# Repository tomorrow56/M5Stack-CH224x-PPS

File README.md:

# M5Stack-CH224x-PPS

An Arduino library and sample sketch collection for controlling CH224A/CH224Q USB PD controllers via I2C on M5Stack (M5Unified compatible), with USB PD PPS/AVS mode voltage adjustment.

## Features

- **Fixed Voltage Mode**: Select from 5V/9V/12V/15V/20V/28V fixed voltages
- **PPS Mode**: Adjust voltage in 0.1V steps within 5.0V～21.0V range
- **AVS Mode**: Variable voltage setting (16-bit precision)
- **Source Capabilities Analysis**: Detailed display of SRCCAP/EPR_SRCCAP messages
- **PDO Type Identification**: Automatic detection of Fixed/Battery/Variable/PPS Supply
- **CH224A Library**: Reusable library class (`src/CH224A.h`)

## Project Structure

```text
M5Stack-CH224x-PPS/
├── src/
│   ├── CH224A.h          # CH224A library header
│   └── CH224A.cpp        # CH224A library implementation
├── examples/
│   ├── M5Stack_PDtrigger_PPS/             # PD Analyzer with PDO decode
│   └── test/                              # Test and debug sketches
│       ├── M5Stack_CH224A_PPS/            # PPS voltage control (with GUI)
│       ├── CH224A_PDO_Test/               # PDO decode test (serial output)
│       ├── I2C_Scanner/                   # I2C device scanner
│       ├── PPS_Test/                      # PPS voltage sweep test
│       └── Simple_Test/                   # Fixed voltage auto-switch test
├── kicad/                                 # KiCad design files
│   └── M5_PDtrigger_PPS_v2/               # Hardware design v2
├── case/                                  # 3D printable case files
│   └── M5Stack_PDtrigger/                 # M5Stack PD Trigger case
├── README_JP.md           # Japanese documentation
├── README.md             # This file
├── WIRING.md             # Detailed wiring information
└── LICENSE               # MIT license
```

## Hardware Requirements

### Required Components

- **M5Stack** (M5Unified compatible device: Core Basic, Core2, CoreS3, etc.)
- **CH224A/CH224Q** USB PD controller (ESSOP10/DFN10 package)
- **USB Type-C connector**
- **1μF ceramic capacitor** (between VHV-GND)

### Pin Connections

| M5Stack       | CH224A          | Description               |
|---------------|-----------------|---------------------------|
| GPIO21        | Pin 3 (CFG3/SDA)| I2C data line            |
| GPIO22        | Pin 2 (CFG2/SCL)| I2C clock line           |
| GND           | Pin 0 (GND)     | Ground                   |
| GPIO2 (※)    | VBUSEN          | Output enable            |
| GPIO12 (※)   | Pin 10 (PG)     | Power Good input         |

※ Used in sample sketches. Can be changed according to your purpose.

**Important**: When using CFG2/CFG3 pins as I2C, do not connect resistors to these pins (leave them floating).

For detailed wiring information, see [WIRING.md](WIRING.md).

## 3D Printable Case

A custom 3D printable case is available for the M5Stack PD Trigger:

### Files Available

- **`case/M5Stack_PDtrigger/PDtrigger_10mm_224A.stl`** - Main case body (STL format)
- **`case/M5Stack_PDtrigger/PDtrigger_10mm_224A.3mf`** - Main case body (3MF format)
- **`case/M5Stack_PDtrigger/text.stl`** - Text labels/decorations (STL format)

### Printing Recommendations

- **Layer Height**: 0.2mm for quality
- **Infill**: 20-30% 
- **Support**: Required for overhangs
- **Material**: PLA or PETG recommended

The case is designed to accommodate the CH224A/CH224Q PD controller and provide proper mounting for the M5Stack device.

## Software Requirements

### Arduino IDE Setup

1. **Add M5Stack Board Manager**:
   - Arduino IDE → File → Preferences
   - Add to "Additional Board Manager URLs":

     ```text
     https://m5stack.oss-cn-shenzhen.aliyuncs.com/resource/arduino/package_m5stack_index.json
     ```

2. **Install M5Stack Board**:
   - Tools → Board → Boards Manager
   - Search for "M5Stack" and install

3. **Install M5Unified Library**:
   - Sketch → Include Library → Manage Libraries
   - Search for "M5Unified" and install

### Board Settings

- **Board**: M5Stack-Core-ESP32 (or your M5Stack device)
- **Upload Speed**: 921600
- **Flash Frequency**: 80MHz

## Sample Sketches

### M5Stack_PDtrigger_PPS

M5Stack PD Analyzer - Main application for USB PD charger analysis and voltage control.

**Key Features**:

- Fixed voltage mode switching (5V/9V/12V/15V/20V)
- PPS mode voltage adjustment (0.1V steps)
- PDO Decode screen for detailed Source Capabilities display
- Real-time voltage/current measurement and PG (Power Good) display

**Operation**:

- **Button A (Left)**: Decrease voltage / Enter PDO Decode at PDO=0
- **Button B (Center)**: Output ON/OFF toggle
- **Button C (Right)**: Increase voltage / Enter PPS control at PDO=4 / Exit from PDO Decode

### M5Stack_CH224A_PPS

Legacy version of PPS voltage control GUI application.

### test/ Folder

Contains the following test and debug sketches.

#### CH224A_PDO_Test

Debug sketch that outputs PDO data to serial monitor. Displays raw data and parsed results of Source Capabilities.

#### I2C_Scanner

Scans I2C bus and displays device addresses. Used for CH224A connection verification.

#### PPS_Test

Test sketch that automatically sweeps PPS voltage from 5.5V to 20.0V in 0.5V steps.

#### Simple_Test

Basic test sketch that automatically switches fixed voltages (5V→9V→12V→15V→20V→28V) every 2 seconds.

## CH224A Library

Provides a reusable library class in `src/CH224A.h` and `src/CH224A.cpp`.

### Usage Example

```cpp
#include <Wire.h>
#include "src/CH224A.h"

CH224A ch224a;

void setup() {
  Wire.begin(21, 22);
  
  if (ch224a.begin()) {
    // Fixed voltage setting
    ch224a.setVoltage9V();
    
    // PPS voltage setting (9.5V)
    ch224a.setPPSVoltage(9.5);
    
    // AVS voltage setting (12.0V)
    ch224a.setAVSVoltage(12.0);
  }
}
```

### API

| Method                          | Description                           |
|-----------------------------------|---------------------------------------|
| `begin(TwoWire &wire)`            | Initialize and check connection       |
| `isConnected()`                   | Check I2C connection                  |
| `setVoltage5V()` ～ `setVoltage28V()` | Fixed voltage setting            |
| `setFixedVoltage(CH224A_VoltageMode)` | Voltage mode setting             |
| `setPPSVoltage(float voltage)`    | PPS voltage setting (in volts)        |
| `setPPSVoltageRaw(uint8_t value)` | PPS voltage setting (0.1V units)   |
| `setAVSVoltage(float voltage)`    | AVS voltage setting (in volts)        |
| `setAVSVoltageRaw(uint16_t value)`| AVS voltage setting (0.1V units)   |
| `readRegister(reg, &value)`       | Register read                         |
| `writeRegister(reg, value)`       | Register write                        |
| `readSourceCapabilities(data, length)` | Read Source Capabilities      |
| `getPDOCount(header)`             | Get PDO count                         |
| `getPDOType(pdo)`                 | Get PDO type (0:Fixed, 1:Variable, 3:PPS) |
| `parseFixedPDO(pdo, voltage, current)` | Parse Fixed PDO               |
| `parseVariablePDO(pdo, minV, maxV, current)` | Parse Variable PDO         |
| `parsePPSPDO(pdo, minV, maxV, current)` | Parse PPS PDO                  |
| `decodeHeader(header)`           | Decode and display PDO header         |
| `decodePDOs(data, numPDO)`        | Decode and display PDO data           |

## CH224A Technical Specifications

### Supported Protocols

- USB PD3.2 EPR (Extended Power Range)
- USB PD PPS (Programmable Power Supply)
- USB PD AVS (Adjustable Voltage Supply)
- USB PD SPR (Standard Power Range)
- BC1.2

### Electrical Specifications

- **Input Voltage Range**: 4V～30V
- **I2C Communication Speed**: Max 400kHz
- **I2C Address**: 0x22 (default) or 0x23

### Register Map

| Address    | Name                | Description                     |
|------------|---------------------|----------------------------------|
| 0x09       | I2C_STATUS          | I2C status                      |
| 0x0A       | VOLTAGE_CTRL        | Voltage control (0-7)           |
| 0x50       | CURRENT_DATA        | Current data (50mA units)       |
| 0x51-0x52  | AVS_VOLTAGE         | AVS voltage (16-bit)             |
| 0x53       | PPS_VOLTAGE         | PPS voltage (0.1V units)         |
| 0x60-0x7F  | SRCCAP_DATA         | Source Capabilities             |
| 0x80-0x8F  | EPR_SRCCAP_DATA     | EPR Source Capabilities         |

### Voltage Control Register (0x0A) Values

| Value | Mode       |
|-------|------------|
| 0     | 5V Fixed   |
| 1     | 9V Fixed   |
| 2     | 12V Fixed  |
| 3     | 15V Fixed  |
| 4     | 20V Fixed  |
| 5     | 28V Fixed  |
| 6     | PPS Mode   |
| 7     | AVS Mode   |

## Troubleshooting

### CH224A Not Responding

1. Check SDA/SCL wiring
2. Verify I2C address (use `I2C_Scanner` sketch)
3. Ensure no resistors are connected to CFG2/CFG3 pins
4. Add 4.7kΩ pull-up resistors if necessary

### Voltage Not Changing

1. Verify that the USB PD charger supports PPS/AVS
2. Use a USB PD compatible cable
3. Ensure settings are within the charger's supported voltage range

### Screen Not Displaying

1. Verify M5Unified library is properly installed
2. Check that the correct board is selected

## License

MIT License - see [LICENSE](LICENSE) for details

## References

- [CH224A Datasheet](https://wch.cn)
- [M5Stack Official Documentation](https://docs.m5stack.com)
- [M5Unified GitHub](https://github.com/m5stack/M5Unified)
- [USB Power Delivery Specification](https://www.usb.org/usb-charger-pd)

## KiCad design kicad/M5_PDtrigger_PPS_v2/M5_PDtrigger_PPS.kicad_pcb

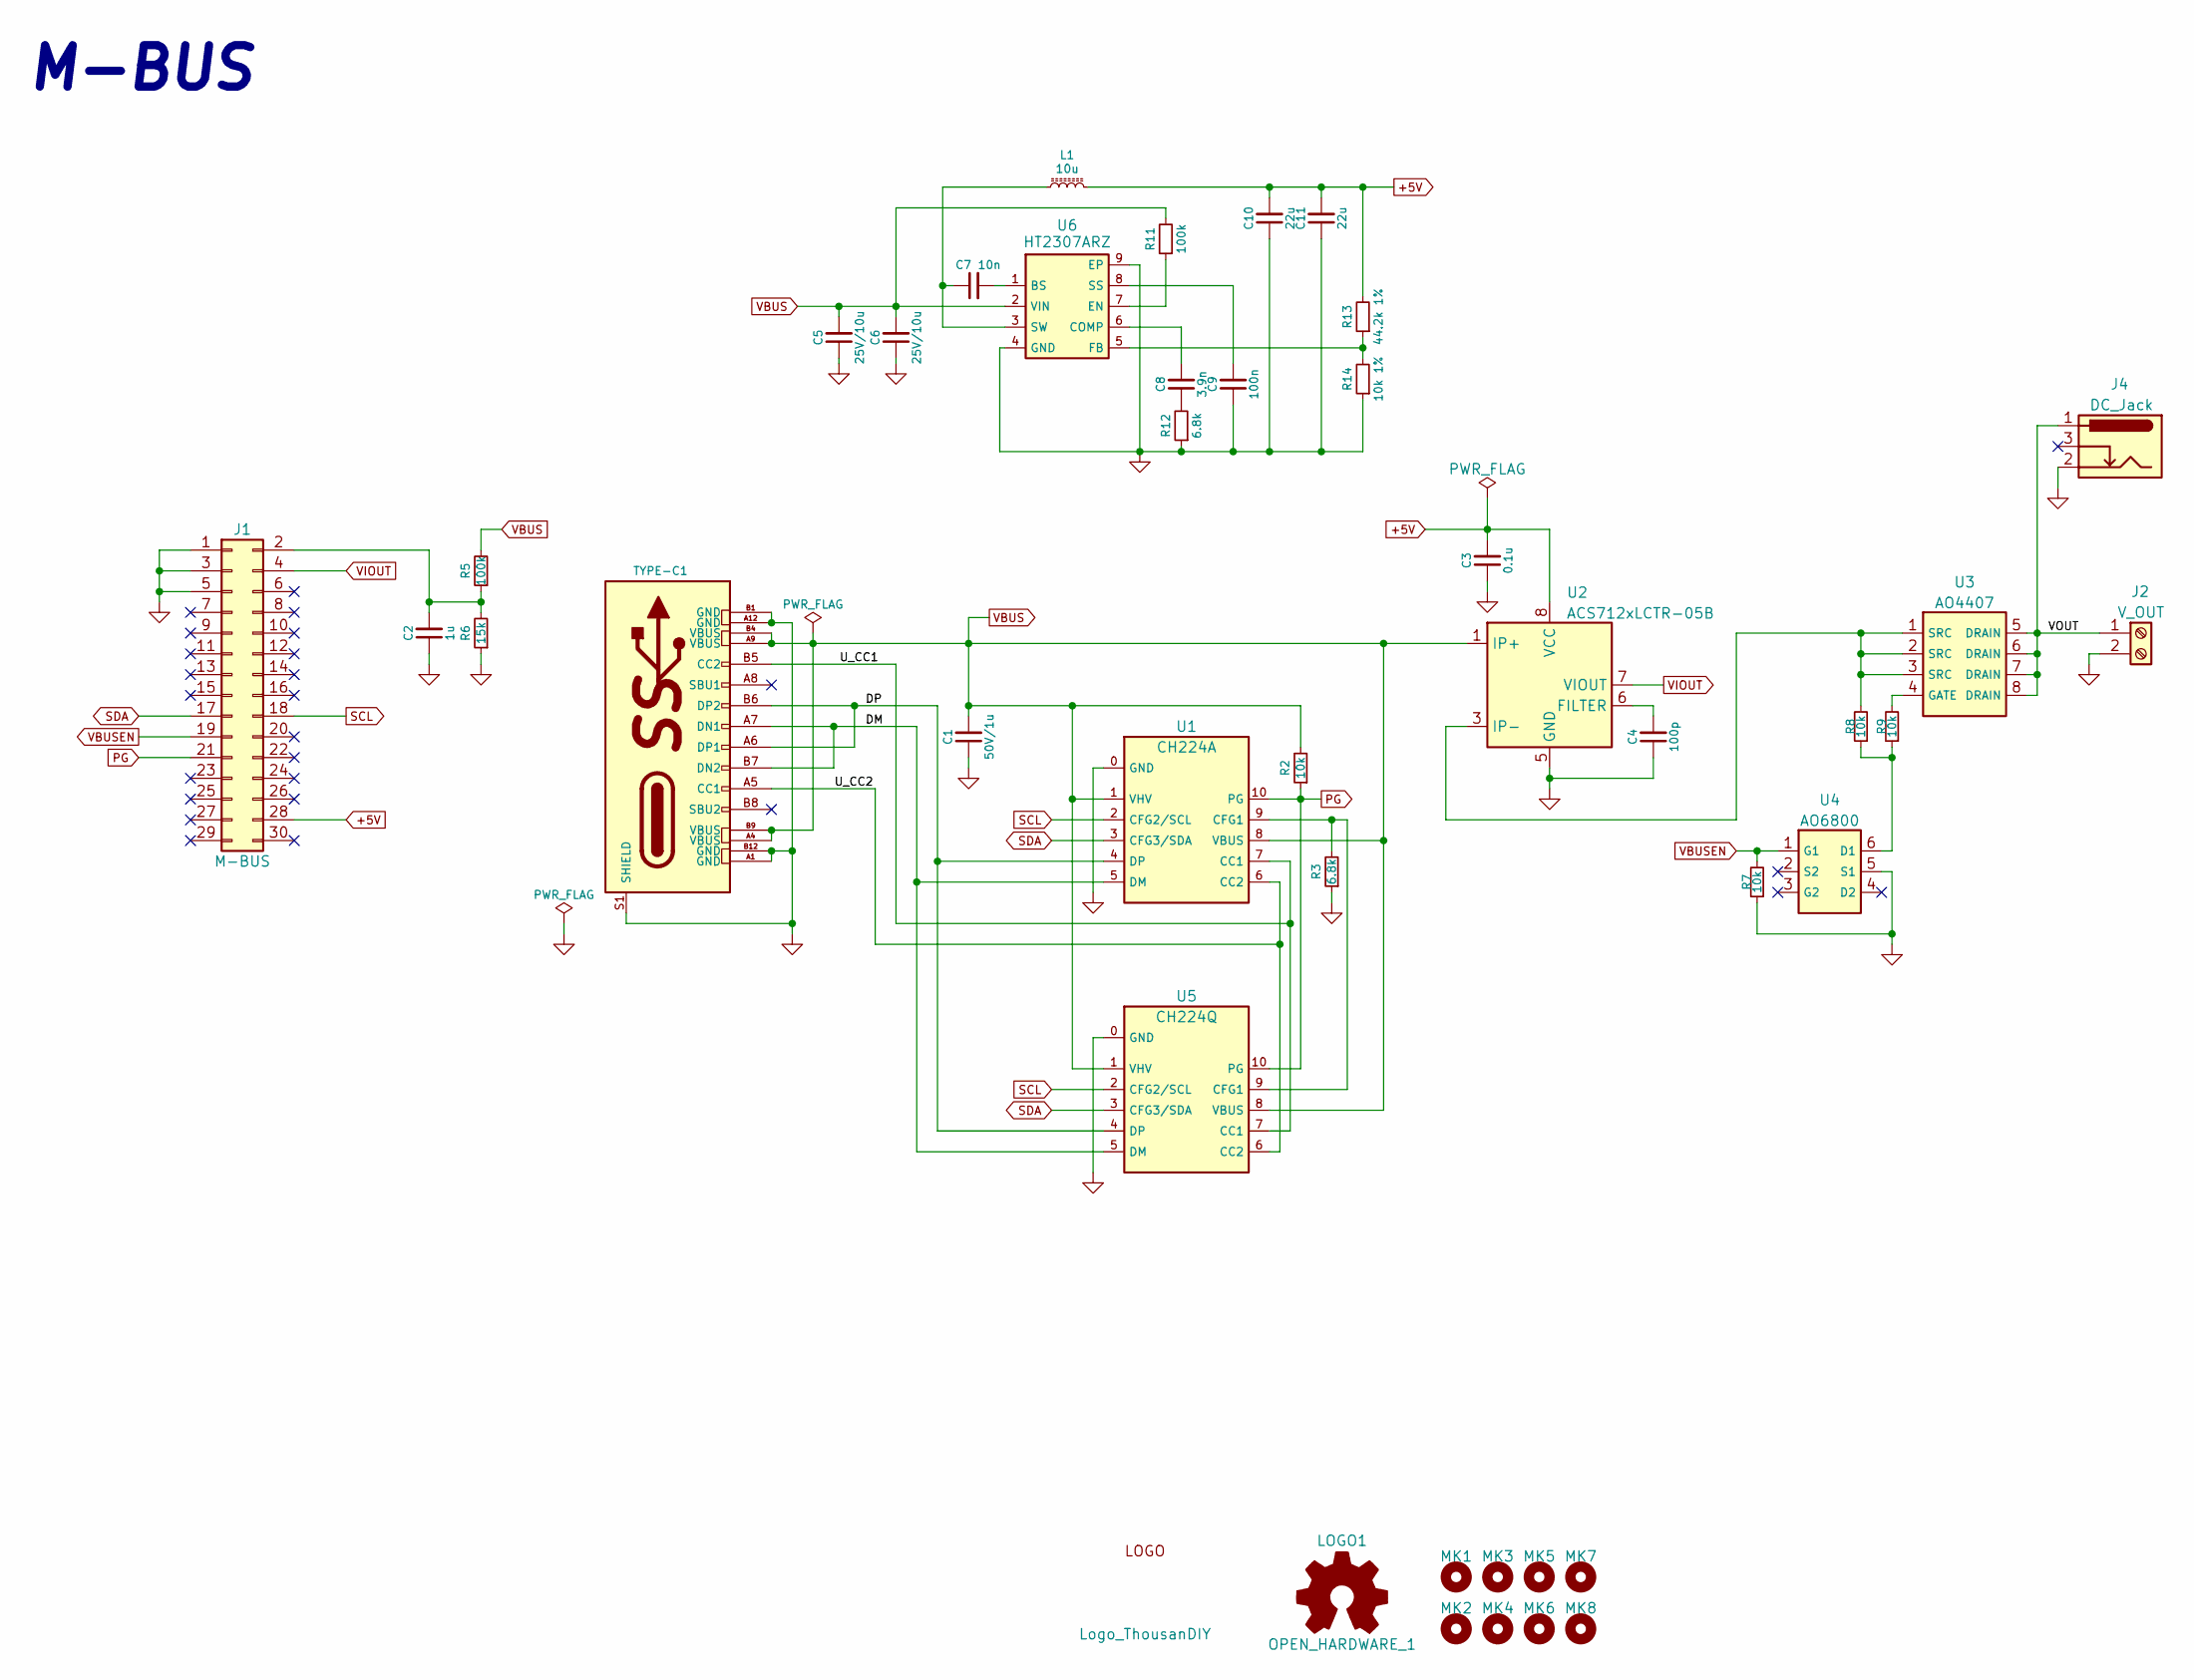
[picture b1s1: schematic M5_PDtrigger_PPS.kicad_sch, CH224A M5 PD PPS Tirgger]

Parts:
C1: 50V/1u; C_0603_1608Metric
C2: 1u; C_0603_1608Metric
C3: 0.1u; C_0603_1608Metric
C4: 100p; C_0603_1608Metric
C5, C6: 25V/10u; C_0603_1608Metric
C7: 10n; C_0603_1608Metric
C8: 3.9n; C_0603_1608Metric
C9: 100n; C_0603_1608Metric
C10, C11: 22u; C_0603_1608Metric
J1: M-BUS; Pin_Header_MBUS_SMD_TH
J2: V_OUT; TB111-2-2
J4: DC_Jack; BarrelJack_Horizontal
L1: 10u; L_Chilisin_BMRB00050518-B
LOGO1: OPEN_HARDWARE_1; OSHW-logo_silkscreen-front_3mm
MK1, MK2, MK3, MK4: Mounting_Hole; MountingHole_M3_mod
MK5, MK6, MK7, MK8: Mounting_Hole; MountingHole_M2_mod
R2, R7, R8, R9: 10k; R_0603_1608Metric
R3, R12: 6.8k; R_0603_1608Metric
R5, R11: 100k; R_0603_1608Metric
R6: 15k; R_0603_1608Metric
R13: 44.2k 1%; R_0603_1608Metric
R14: 10k 1%; R_0603_1608Metric
TYPE-C1: TYPE-C-31-M-12; USB_C_Receptacle_HRO_TYPE-C-31-M-12
U1: CH224A; ESSOP-10_3.9x4.9mm_P1.00mm_ThermalVia
U2: ACS712xLCTR-05B; SOIC-8_3.9x4.9mm_P1.27mm
U3: AO4407; SOP-8_3.9x4.9mm_P1.27mm
U4: AO6800; SOT-23-6
U5: CH224Q; DFN-10_2x2mm_P0.4mm_ThermalVia
U6: HT2307ARZ; HSOP-8-1EP_3.9x4.9mm_P1.27mm_EP2.41x3.1mm_ThermalVias
logo2: Logo_ThousanDIY; TDIY-LOGO-S

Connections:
+5V: C3.2, C10.2, C11.2, J1.28, L1.2, R13.2, U2.8 (VCC)
/DM: TYPE-C1.A7 (DN1), TYPE-C1.B7 (DN2), U1.5 (DM), U5.5 (DM)
/DP: TYPE-C1.A6 (DP1), TYPE-C1.B6 (DP2), U1.4 (DP), U5.4 (DP)
/U_CC1: TYPE-C1.B5 (CC2), U1.7 (CC1), U5.7 (CC1)
/U_CC2: TYPE-C1.A5 (CC1), U1.6 (CC2), U5.6 (CC2)
/VOUT: J2.1, J4.1, U3.5 (DRAIN), U3.6 (DRAIN), U3.7 (DRAIN), U3.8 (DRAIN)
GND: C1.1, C2.1, C3.1, C4.1, C5.1, C6.1, C9.1, C10.1, C11.1, J1.1, J1.3, J1.5, J2.2, J4.2, R3.1, R6.1, R7.1, R12.1, R14.1, TYPE-C1.A1 (GND), TYPE-C1.A12 (GND), TYPE-C1.B1 (GND), TYPE-C1.B12 (GND), TYPE-C1.S1 (SHIELD), U1.0 (GND), U2.5 (GND), U4.5 (S1), U5.0 (GND), U6.4 (GND), U6.9 (EP)
unnamed: C8.1, R12.2
unnamed: C2.2, J1.2, R5.1, R6.2
unnamed: R8.2, U2.3 (IP-), U2.4 (IP-), U3.1 (SRC), U3.2 (SRC), U3.3 (SRC)
unnamed: R3.2, U1.9 (CFG1), U5.9 (CFG1)
unnamed: C4.2, U2.6 (FILTER)
unnamed: R9.2, U3.4 (GATE)
unnamed: R8.1, R9.1, U4.6 (D1)
unnamed: C7.2, U6.1 (BS)
unnamed: C8.2, U6.6 (COMP)
unnamed: R11.1, U6.7 (EN)
unnamed: R13.1, R14.2, U6.5 (FB)
unnamed: C9.2, U6.8 (SS)
unnamed: C7.1, L1.1, U6.3 (SW)
PG: J1.21, R2.1, U1.10 (PG), U5.10 (PG)
SCL: J1.18, U1.2 (CFG2/SCL), U5.2 (CFG2/SCL)
SDA: J1.17, U1.3 (CFG3/SDA), U5.3 (CFG3/SDA)
VBUS: C1.2, C5.2, C6.2, R2.2, R5.2, R11.2, TYPE-C1.A4 (VBUS), TYPE-C1.A9 (VBUS), TYPE-C1.B4 (VBUS), TYPE-C1.B9 (VBUS), U1.1 (VHV), U1.8 (VBUS), U2.1 (IP+), U2.2 (IP+), U5.1 (VHV), U5.8 (VBUS), U6.2 (VIN)
VBUSEN: J1.19, R7.2, U4.1 (G1)
VIOUT: J1.4, U2.7 (VIOUT)

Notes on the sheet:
M-BUS

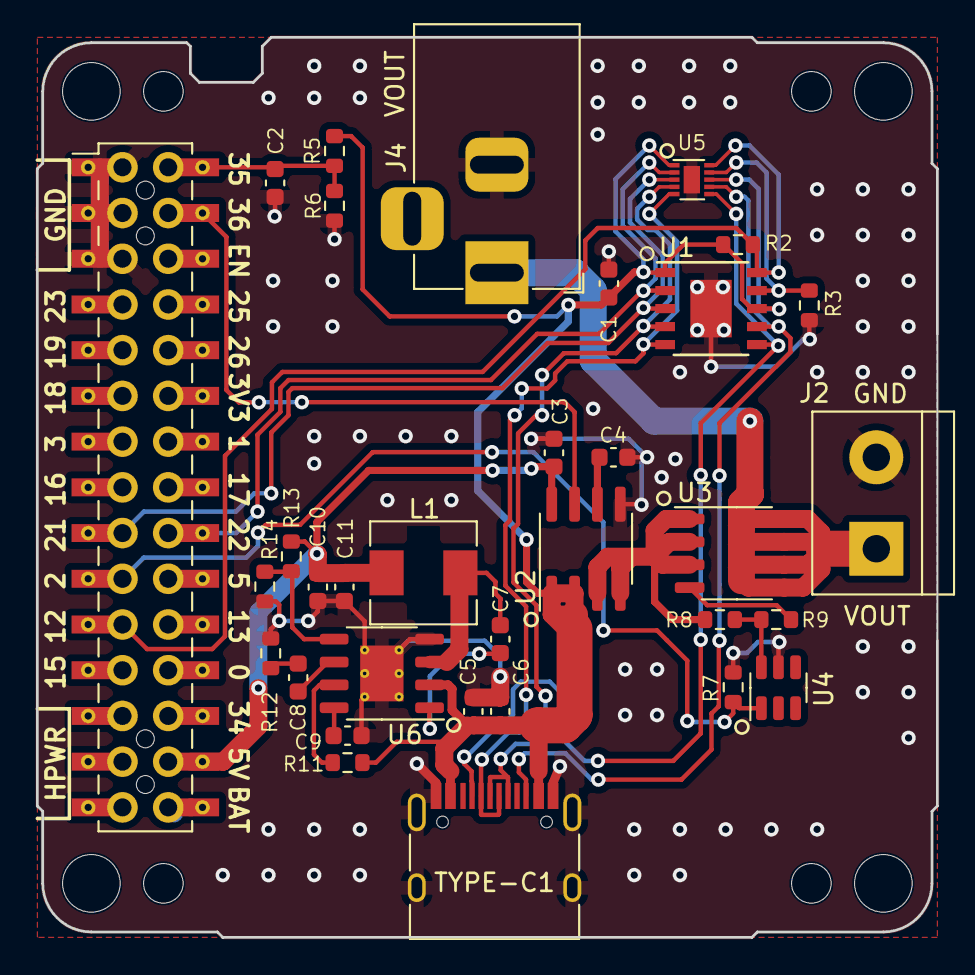
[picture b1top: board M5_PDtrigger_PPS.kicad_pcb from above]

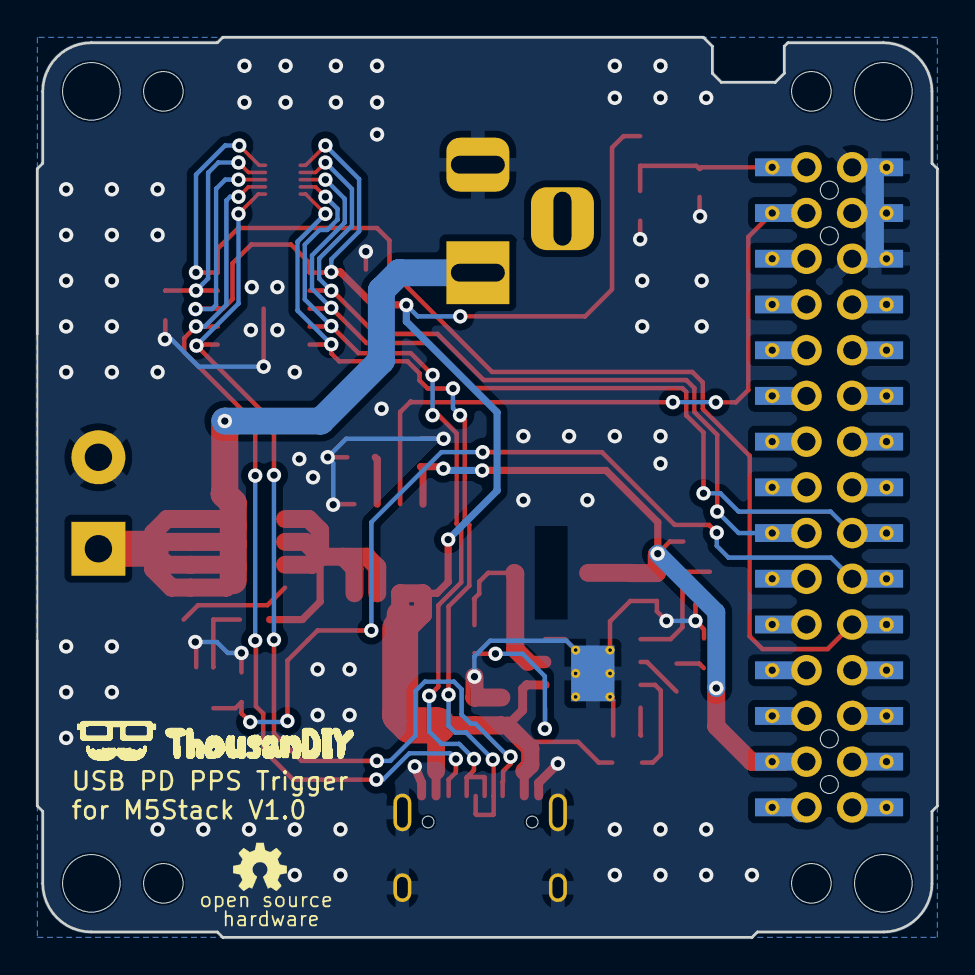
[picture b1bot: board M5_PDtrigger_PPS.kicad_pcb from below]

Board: 2 copper layers, 50.0 x 50.0 mm, 43 parts (2 on the bottom side), 26 nets.

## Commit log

2025-11-18 Initial commit: M5Stack CH224A PPS controller
    - Add main sketch with direct I2C control
    - Add library-based sketch for better maintainability
    - Add CH224A library with PPS/AVS/fixed voltage support
    - Add comprehensive documentation (README, WIRING, PROJECT_OVERVIEW)
    - Add example sketches for testing and I2C scanning
    - Add proper .gitignore for macOS/Arduino/IDE files
2025-11-25 Add Source Capabilities Reader example and remove duplicate library example
    - Add M5Stack_CH224A_Source_Capabilities example with detailed PDO analysis
    - Remove duplicate M5Stack_CH224A_PPS_Library example
    - Clean up macOS ._ files from repository
2025-11-25 Update documentation to reflect current repository structure
    - Add Source Capabilities analysis features to README.md
    - Update PROJECT_OVERVIEW.md with new examples and library structure
    - Document CH224A library usage and API
    - Update version history to v1.1.0
    - Fix file paths and project organization
2025-11-25 Update examples to M5Unified and clean up metadata files
    - Convert all examples from M5Stack.h to M5Unified.h
    - Replace M5.Lcd with M5.Display for M5Unified compatibility
    - Add comprehensive macOS metadata files to .gitignore
    - Remove all ._ files from repository
    - Update pin configurations and I2C handling
    - Improve PPS voltage range and step precision
2025-12-07 Fix PDO byte order and add serial debug output for Source Capabilities
    - Correct PDO data byte order from big-endian to little-endian format
    - Add Serial.begin(115200) initialization in setup()
    - Add formatted serial output for received PD data (4 bytes per line)
    - Fix bit shift positions in PDO parsing to match USB-PD specification
2025-12-07 Remove PROJECT_OVERVIEW.md and consolidate documentation into README.md
    - Delete PROJECT_OVERVIEW.md (271 lines of duplicate documentation)
    - Rewrite README.md with improved structure and M5Unified focus
    - Add project structure tree showing src/ and examples/ directories
    - Document all example sketches with usage instructions
    - Add CH224A library usage examples and API reference
    - Update hardware requirements to include CH224K support
2025-12-07 Add Message Header display mode and improve EPR_SRCCAP PDO parsing
    - Add DISPLAY_HEADER mode to show USB-PD message header details
    - Change button operations: A=update, B=cycle modes (SRCCAP/EPR/HEADER), C=show header
    - Implement decodeHeader() to parse message header and extract PDO count
    - Add checkEPRCapable() to detect EPR Mode Capable flag from PDO1 bit[23]
    - Fix EPR PDO offset calculation based on actual SRCCAP PDO count
    - Improve EPR PDO detection with proper little-endian byte order
2026-02-08 v1.0.0: Add PDO parsing functionality and M5Stack PD Analyzer
    - Add PDO parsing functions to CH224A library (readSourceCapabilities, getPDOCount, parseFixedPDO, parseVariablePDO, parsePPSPDO, getPDOType, decodeHeader, decodePDOs)
    - Add M5Stack_PDtrigger_PPS example with PDO decode screen
    - Move test sketches to examples/test/ folder
    - Add keywords.txt and library.properties
    - Add README.md (English) and README_JP.md (Japanese)
    - Force PDO=0 (5V) on startup
2026-02-15 Enhance M5Stack PD Analyzer UI and interaction
    - Add horizontal PDO list with cyan highlight for selected mode
    - Implement framed sub-window style for PDO Decode screen
    - Fix flickering by conditional redraw on mode entry only
    - Display unsupported PDOs in gray text in normal mode list
    - Add long-press auto increment/decrement for PPS voltage (100mV steps)
    - Prevent PPS mode entry if charger does not support PPS
2026-05-30 Update README_JP.md for CH224Q controller
2026-05-30 Fix CH224A datasheet link in README_JP.md
    Updated the link for the CH224A datasheet to the official site.
2026-05-30 Update project structure and documentation
    - Move M5Stack_CH224A_PPS to examples/test/ folder
    - Remove Mac-generated ._ files
    - Update README.md and README_JP.md to reflect current folder structure
    - Fix markdown lint errors (code block language, spacing)
2026-05-30 Update CH224K to CH224Q in documentation
    - Fix chip model reference in README.md and README_JP.md
    - Minor table alignment improvements for Japanese text
2026-05-30 Complete CH224K to CH224Q update across all files
    - Update library.properties: CH224A/CH224K → CH224A/CH224Q
    - Update keywords.txt: CH224K → CH224Q
    - Update M5Stack_PDtrigger_PPS.ino comment header
    - Fix README.md table alignment and markdown formatting
    - Maintain consistency with KiCad hardware design (CH224Q)
2026-05-31 Add 3D printable case files and documentation
    - Add case/ folder with M5Stack PD Trigger 3D print files
    - Include STL and 3MF format files for main case body and text labels
    - Update README.md and README_JP.md with 3D printing section
    - Add printing recommendations and file descriptions
    - Update project structure documentation
